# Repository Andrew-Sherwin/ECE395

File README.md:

# ECE395
Advanced Digital Projects Laboratory
Project: Digital Target System

The Digital Target System folder contains 6 files:
1. Digital Target System Report.pdf
	- This contains the report documenting the design of the product. 
2. DigitalTargetSystem Code (folder)
	- This contains the C code necessary to program the product (if reprogramming or a new revision is needed). 
3. PCB Art (folder)
	- This contains some ART for the silkscreens.
4. PCB with Art (folder)
	- This contains Rev10 PCB KiCad files with Art (unorganized). 
5. Rev8 KiCad Files (folder)
	- This contains Rev8 PCB. A version of the PCB without switches. Power is from the barrel-jack ONLY. 
6. Rev10 KiCad Files (folder)
	- This contains Rev10 PCB. A versino of the PCB wit switches. Power can be from barrel-jack or alternate power source such as a DC Power Supply. 

Updated: December 10, 2023 19:24 CST - Andrew Sherwin

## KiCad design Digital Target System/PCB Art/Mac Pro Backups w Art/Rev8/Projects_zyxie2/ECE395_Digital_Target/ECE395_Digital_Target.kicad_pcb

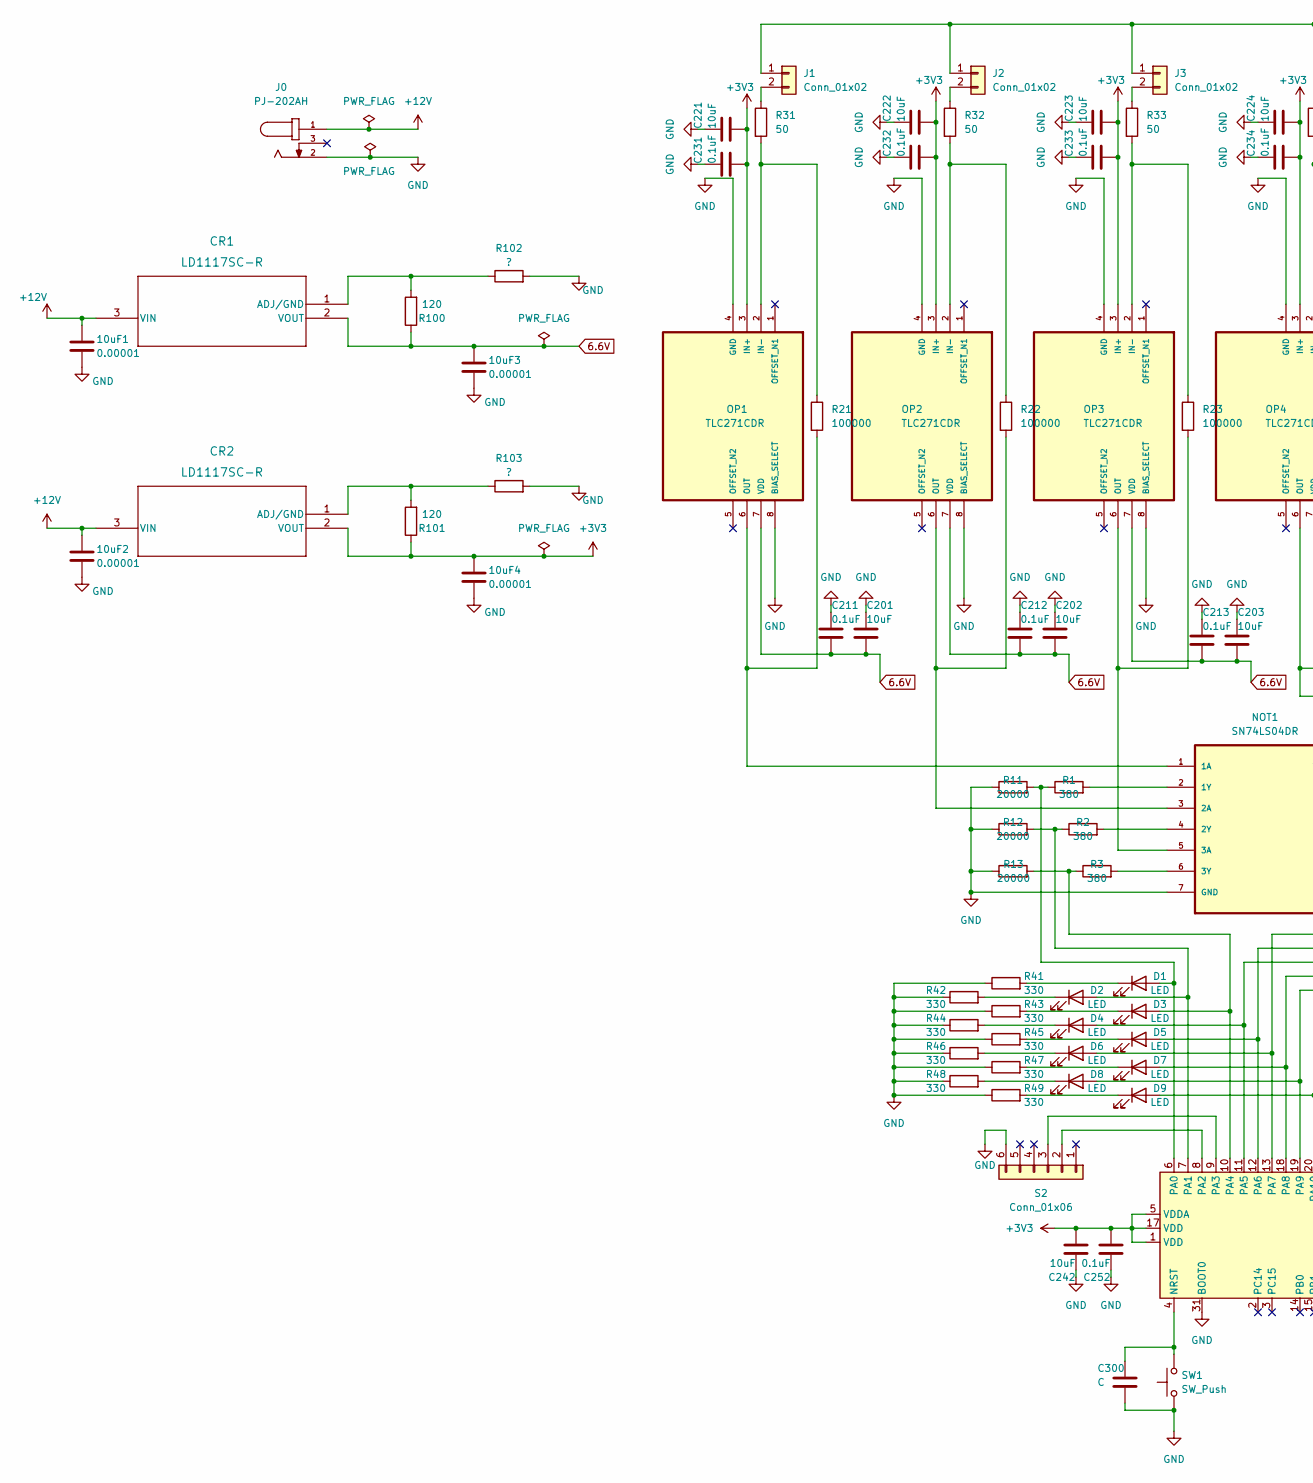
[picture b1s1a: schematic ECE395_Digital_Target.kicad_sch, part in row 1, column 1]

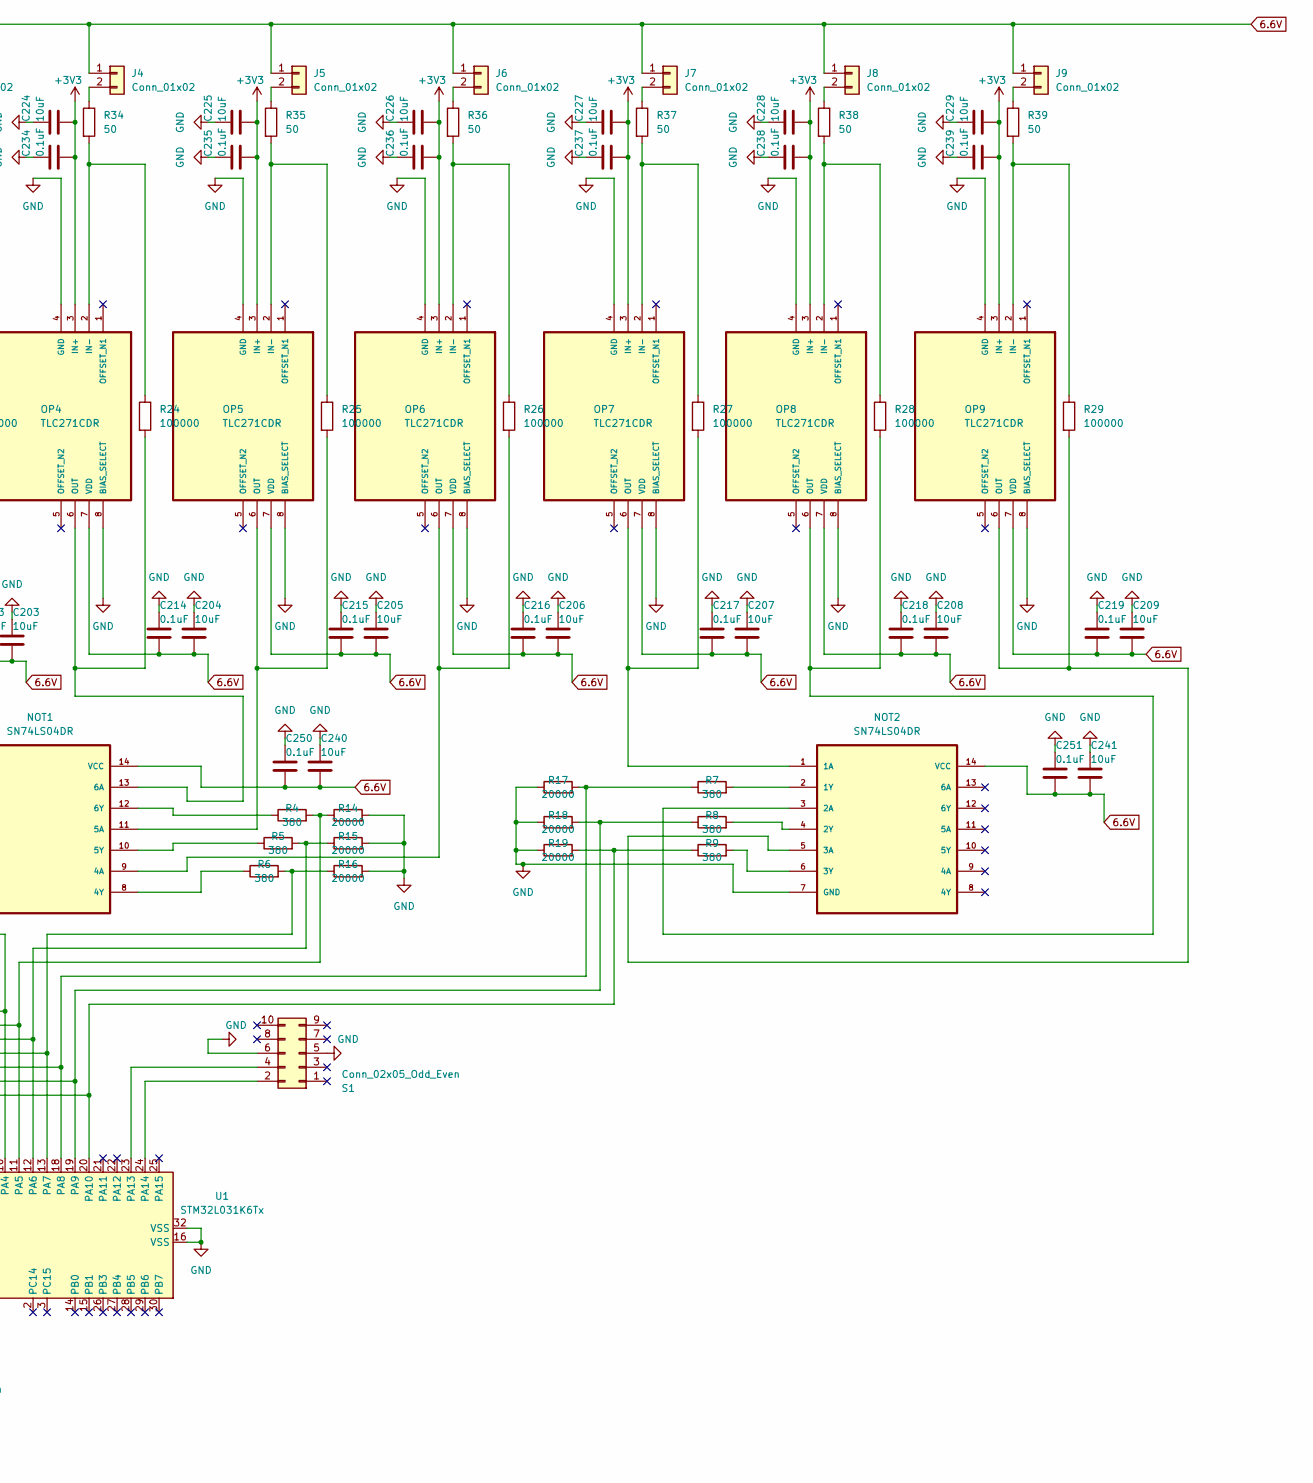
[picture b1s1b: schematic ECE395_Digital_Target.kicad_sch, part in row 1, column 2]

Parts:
10uF1, 10uF2, 10uF3, 10uF4: 0.00001; C_0805_2012Metric_Pad1.18x1.45mm_HandSolder
C201, C202, C203, C204, C205, C206, C207, C208, C209, C221, C222, C223, C224, C225, C226, C227, C228, C229, C240, C241, C242: 10uF; C_0805_2012Metric_Pad1.18x1.45mm_HandSolder
C211, C212, C213, C214, C215, C216, C217, C218, C219, C231, C232, C233, C234, C235, C236, C237, C238, C239, C250, C251, C252: 0.1uF; C_0805_2012Metric_Pad1.18x1.45mm_HandSolder
C300: C; C_0805_2012Metric_Pad1.18x1.45mm_HandSolder
CR1, CR2: LD1117SC-R; LD1117SC_R
D1, D2, D3, D4, D5, D6, D7, D8, D9: LED; LED_0805_2012Metric_Pad1.15x1.40mm_HandSolder
J0: PJ-202AH; PJ_202AH; PART_REV 1.02
J1, J2, J3, J4, J5, J6, J7, J8, J9: Conn_01x02; PinSocket_1x02_P2.54mm_Horizontal
NOT1, NOT2: SN74LS04DR
OP1, OP2, OP3, OP4, OP5, OP6, OP7, OP8, OP9: TLC271CDR
R1, R2, R3, R4, R5, R6, R7, R8, R9: 380; R_0805_2012Metric_Pad1.20x1.40mm_HandSolder
R11, R12, R13, R14, R15, R16, R17, R18, R19: 20000; R_0805_2012Metric_Pad1.20x1.40mm_HandSolder
R21, R22, R23, R24, R25, R26, R27, R28, R29: 100000; R_0805_2012Metric_Pad1.20x1.40mm_HandSolder
R31, R32, R33, R34, R35, R36, R37, R38, R39: 50; R_0805_2012Metric_Pad1.20x1.40mm_HandSolder
R41, R42, R43, R44, R45, R46, R47, R48, R49: 330; R_0805_2012Metric_Pad1.20x1.40mm_HandSolder
R100, R101: 120; R_0805_2012Metric_Pad1.20x1.40mm_HandSolder
R102, R103: ?; R_0805_2012Metric_Pad1.20x1.40mm_HandSolder
S1: Conn_02x05_Odd_Even; PinSocket_2x05_P2.54mm_Vertical
S2: Conn_01x06; PinSocket_1x06_P2.54mm_Horizontal
SW1: SW_Push; SW_PUSH_6mm_H4.3mm
U1: STM32L031K6Tx; LQFP-32_7x7mm_P0.8mm

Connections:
6.6V: 10uF3.1, C201.2, C202.2, C203.2, C204.2, C205.2, C206.2, C207.2, C208.2, C209.2, C211.2, C212.2, C213.2, C214.2, C215.2, C216.2, C217.2, C218.2, C219.2, C240.2, C241.2, C250.2, C251.2, CR1.2 (VOUT), J1.1, J2.1, J3.1, J4.1, J5.1, J6.1, J7.1, J8.1, J9.1, NOT1.14 (VCC), NOT2.14 (VCC), OP1.7 (VDD), OP2.7 (VDD), OP3.7 (VDD), OP4.7 (VDD), OP5.7 (VDD), OP6.7 (VDD), OP7.7 (VDD), OP8.7 (VDD), OP9.7 (VDD), R100.1
+3V3: 10uF4.1, C221.2, C222.2, C223.2, C224.2, C225.2, C226.2, C227.2, C228.2, C229.2, C231.2, C232.2, C233.2, C234.2, C235.2, C236.2, C237.2, C238.2, C239.2, C242.2, C252.2, CR2.2 (VOUT), OP1.3 (IN+), OP2.3 (IN+), OP3.3 (IN+), OP4.3 (IN+), OP5.3 (IN+), OP6.3 (IN+), OP7.3 (IN+), OP8.3 (IN+), OP9.3 (IN+), R101.1, U1.1 (VDD), U1.5 (VDDA), U1.17 (VDD)
+12V: 10uF1.1, 10uF2.1, CR1.3 (VIN), CR2.3 (VIN), J0.1
GND: 10uF1.2, 10uF2.2, 10uF3.2, 10uF4.2, C201.1, C202.1, C203.1, C204.1, C205.1, C206.1, C207.1, C208.1, C209.1, C211.1, C212.1, C213.1, C214.1, C215.1, C216.1, C217.1, C218.1, C219.1, C221.1, C222.1, C223.1, C224.1, C225.1, C226.1, C227.1, C228.1, C229.1, C231.1, C232.1, C233.1, C234.1, C235.1, C236.1, C237.1, C238.1, C239.1, C240.1, C241.1, C242.1, C250.1, C251.1, C252.1, C300.2, J0.2, NOT1.7 (GND), NOT2.7 (GND), OP1.4 (GND), OP1.8 (BIAS_SELECT), OP2.4 (GND), OP2.8 (BIAS_SELECT), OP3.4 (GND), OP3.8 (BIAS_SELECT), OP4.4 (GND), OP4.8 (BIAS_SELECT), OP5.4 (GND), OP5.8 (BIAS_SELECT), OP6.4 (GND), OP6.8 (BIAS_SELECT), OP7.4 (GND), OP7.8 (BIAS_SELECT), OP8.4 (GND), OP8.8 (BIAS_SELECT), OP9.4 (GND), OP9.8 (BIAS_SELECT), R11.1, R12.1, R13.1, R14.2, R15.2, R16.2, R17.1, R18.1, R19.1, R41.1, R42.1, R43.1, R44.1, R45.1, R46.1, R47.1, R48.1, R49.1, R102.2, R103.2, S1.5, S1.6, S2.6, SW1.1, U1.16 (VSS), U1.31 (BOOT0), U1.32 (VSS)
unnamed: C300.1, SW1.2, U1.4 (NRST)
unnamed: CR1.1 (ADJ/GND), R100.2, R102.1
unnamed: CR2.1 (ADJ/GND), R101.2, R103.1
unnamed: D1.1 (K), R41.2
unnamed: D1.2 (A), R1.1, R11.2, U1.6 (PA0)
unnamed: D2.1 (K), R42.2
unnamed: D2.2 (A), R2.1, R12.2, U1.7 (PA1)
unnamed: D3.1 (K), R43.2
unnamed: D3.2 (A), R3.1, R13.2, U1.10 (PA4)
unnamed: D4.1 (K), R44.2
unnamed: D4.2 (A), R4.2, R14.1, U1.11 (PA5)
unnamed: D5.1 (K), R45.2
unnamed: D5.2 (A), R5.2, R15.1, U1.12 (PA6)
unnamed: D6.1 (K), R46.2
unnamed: D6.2 (A), R6.2, R16.1, U1.13 (PA7)
unnamed: D7.1 (K), R47.2
unnamed: D7.2 (A), R7.1, R17.2, U1.18 (PA8)
unnamed: D8.1 (K), R48.2
unnamed: D8.2 (A), R8.1, R18.2, U1.19 (PA9)
unnamed: D9.1 (K), R49.2
unnamed: D9.2 (A), R9.1, R19.2, U1.20 (PA10)
unnamed: J1.2, R31.1
unnamed: J2.2, R32.1
unnamed: J3.2, R33.1
unnamed: J4.2, R34.1
unnamed: J5.2, R35.1
unnamed: J6.2, R36.1
unnamed: J7.2, R37.1
unnamed: J8.2, R38.1
unnamed: J9.2, R39.1
unnamed: NOT1.1 (1A), OP1.6 (OUT), R21.2
unnamed: NOT1.2 (1Y), R1.2
unnamed: NOT1.3 (2A), OP2.6 (OUT), R22.2
unnamed: NOT1.4 (2Y), R2.2
unnamed: NOT1.5 (3A), OP3.6 (OUT), R23.2
unnamed: NOT1.6 (3Y), R3.2
unnamed: NOT1.8 (4Y), R6.1
unnamed: NOT1.9 (4A), OP6.6 (OUT), R26.2
unnamed: NOT1.10 (5Y), R5.1
unnamed: NOT1.11 (5A), OP5.6 (OUT), R25.2
unnamed: NOT1.12 (6Y), R4.1
unnamed: NOT1.13 (6A), OP4.6 (OUT), R24.2
unnamed: NOT2.1 (1A), OP7.6 (OUT), R27.2
unnamed: NOT2.2 (1Y), R7.2
unnamed: NOT2.3 (2A), OP8.6 (OUT), R28.2
unnamed: NOT2.4 (2Y), R8.2
unnamed: NOT2.5 (3A), OP9.6 (OUT), R29.2
unnamed: NOT2.6 (3Y), R9.2
unnamed: OP1.2 (IN-), R21.1, R31.2
unnamed: OP2.2 (IN-), R22.1, R32.2
unnamed: OP3.2 (IN-), R23.1, R33.2
unnamed: OP4.2 (IN-), R24.1, R34.2
unnamed: OP5.2 (IN-), R25.1, R35.2
unnamed: OP6.2 (IN-), R26.1, R36.2
unnamed: OP7.2 (IN-), R27.1, R37.2
unnamed: OP8.2 (IN-), R28.1, R38.2
unnamed: OP9.2 (IN-), R29.1, R39.2
unnamed: S1.2, U1.24 (PA14)
unnamed: S1.4, U1.23 (PA13)
unnamed: S2.2, U1.8 (PA2)
unnamed: S2.3, U1.9 (PA3)

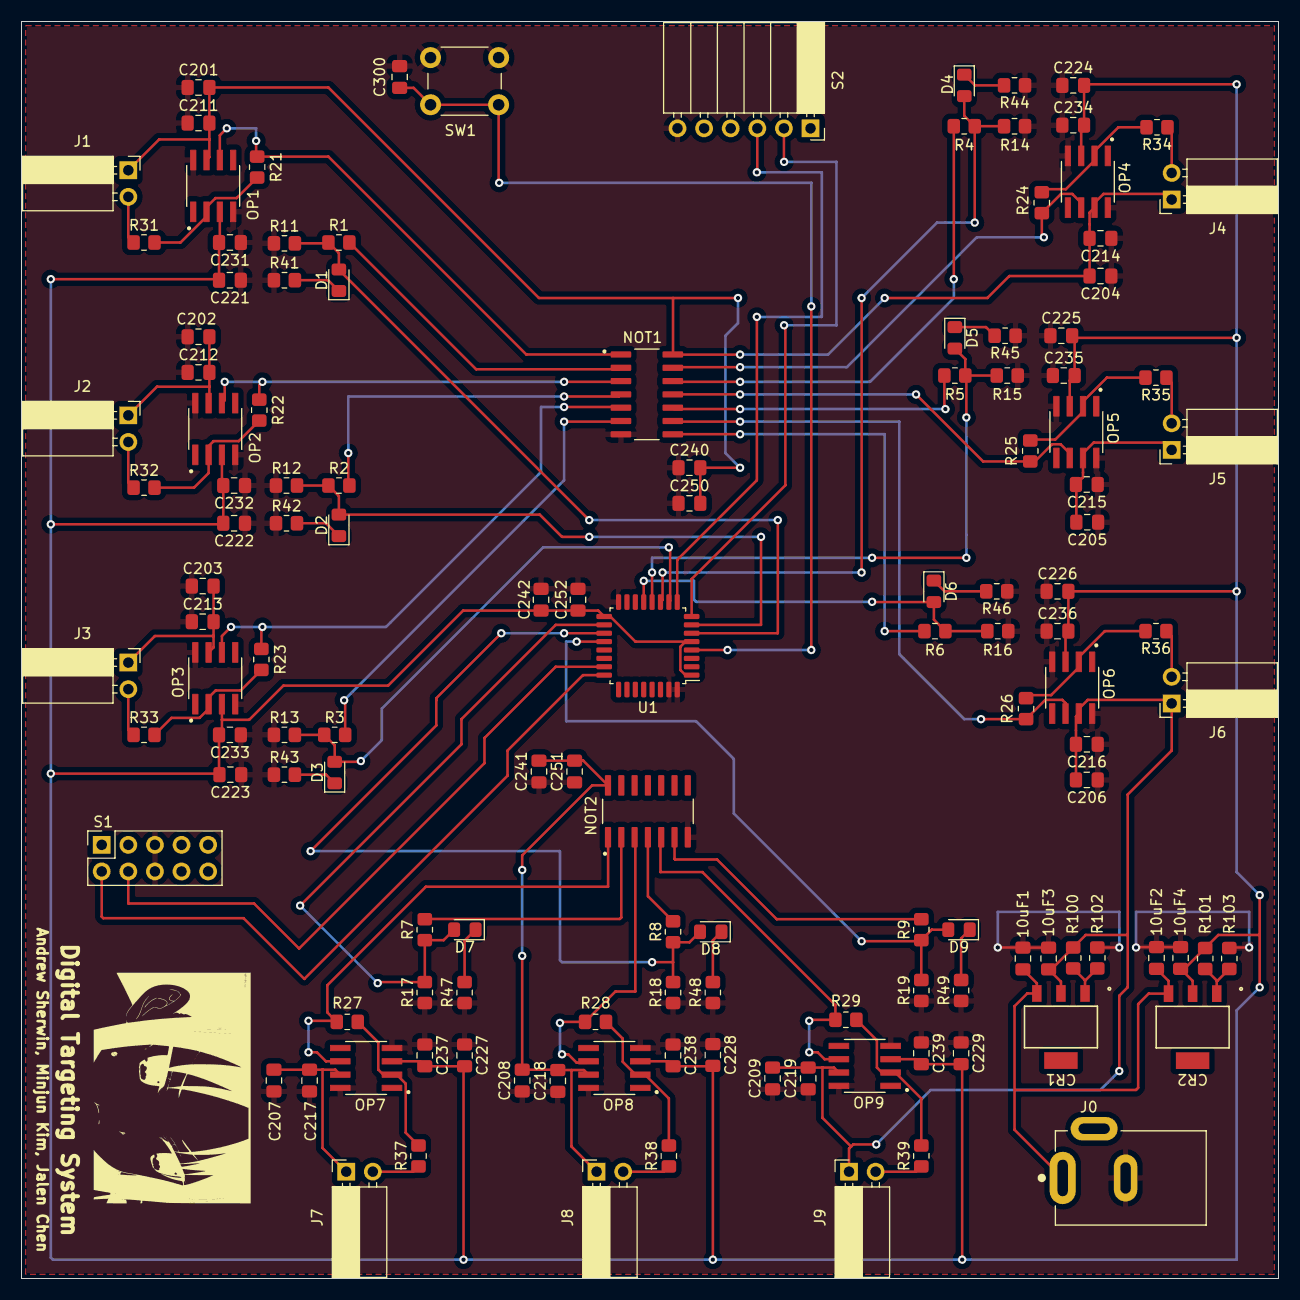
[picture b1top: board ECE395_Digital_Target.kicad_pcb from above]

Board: 2 copper layers, 120.0 x 120.0 mm, 132 parts (0 on the bottom side), 65 nets.

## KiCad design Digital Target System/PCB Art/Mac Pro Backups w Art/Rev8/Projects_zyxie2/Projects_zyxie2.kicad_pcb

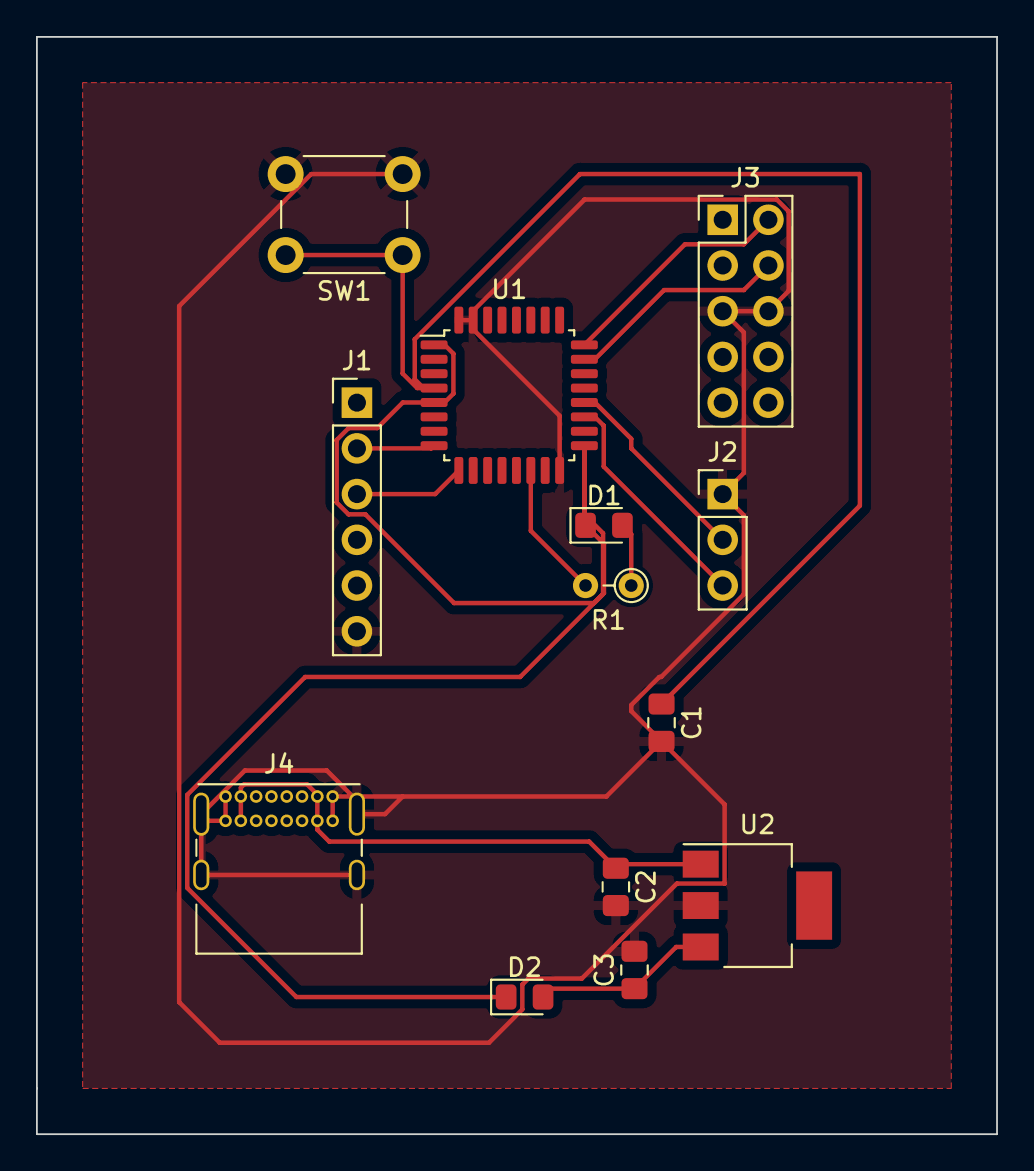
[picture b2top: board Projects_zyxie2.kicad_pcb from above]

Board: 2 copper layers, 53.3 x 61.0 mm, 13 parts (0 on the bottom side), 13 nets.

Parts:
C1, C2, C3: 0.000001; C_0805_2012Metric_Pad1.18x1.45mm_HandSolder
D1, D2: LED; LED_0805_2012Metric_Pad1.15x1.40mm_HandSolder
J1: TTL Adapter; PinHeader_1x06_P2.54mm_Vertical
J2: I2C; PinHeader_1x03_P2.54mm_Vertical
J3: ST_Link V2 Programmer; PinHeader_2x05_P2.54mm_Vertical
J4: USB_C_Receptacle_USB2.0; USB_C_Receptacle_GCT_USB4085
R1: 330; R_Axial_DIN0204_L3.6mm_D1.6mm_P2.54mm_Vertical
SW1: SW_Push; SW_PUSH_6mm_H4.3mm
U1: STM32L031K6Tx; LQFP-32_7x7mm_P0.8mm
U2: TC1262-33; SOT-223

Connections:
+3V3: D1.1 (K), D2.1 (K), U1.1 (VDD), U1.5 (VDDA), U1.17 (VDD)
+5V: C2.1, J4.A4 (VBUS), J4.A9 (VBUS), J4.B4 (VBUS), J4.B9 (VBUS), U2.1 (VI)
GND: C1.2, C2.2, C3.2, J1.6, J2.1, J3.5, J3.6, J4.A1 (GND), J4.A12 (GND), J4.B1 (GND), J4.B12 (GND), J4.S1 (SHIELD), SW1.2, U1.16 (VSS), U1.31 (BOOT0), U1.32 (VSS), U2.2 (GND)
unnamed: D1.2 (A), R1.1
unnamed: C3.1, D2.2 (A), U2.3 (VO)
unnamed: J1.2, U1.8 (PA2)
unnamed: J1.3, U1.9 (PA3)
unnamed: J2.2, U1.20 (PA10)
unnamed: J2.3, U1.19 (PA9)
unnamed: J3.2, U1.24 (PA14)
unnamed: J3.4, U1.23 (PA13)
unnamed: C1.1, SW1.1, U1.4 (NRST)
unnamed: R1.2, U1.14 (PB0)

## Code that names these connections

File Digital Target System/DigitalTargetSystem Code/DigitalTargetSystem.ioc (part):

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Mcu.Name=STM32L031K(4-6)Tx
Mcu.Package=LQFP32
Mcu.UserName=STM32L031K6Tx
PA0-CK_IN.Signal=GPIO_Input
PA1.Signal=GPIO_Input
PA10.Signal=GPIO_Input
PA13.Mode=Serial_Wire
PA13.Signal=SYS_SWDIO
PA14.Mode=Serial_Wire
PA14.Signal=SYS_SWCLK
PA2.Mode=Asynchronous
PA2.Signal=LPUART1_TX
PA3.Mode=Asynchronous
PA3.Signal=LPUART1_RX
PA4.Signal=GPIO_Input
PA5.Signal=GPIO_Input
PA6.Signal=GPIO_Input
PA7.Signal=GPIO_Input
PA8.Signal=GPIO_Input
PA9.Signal=GPIO_Input
RCC.HSE_VALUE=8000000
RCC.SYSCLKFreq_VALUE=2097000
board=custom

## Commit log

2023-12-11 Digital Target System Push
2023-12-11 Report Commit
2023-12-11 Report Update V4
